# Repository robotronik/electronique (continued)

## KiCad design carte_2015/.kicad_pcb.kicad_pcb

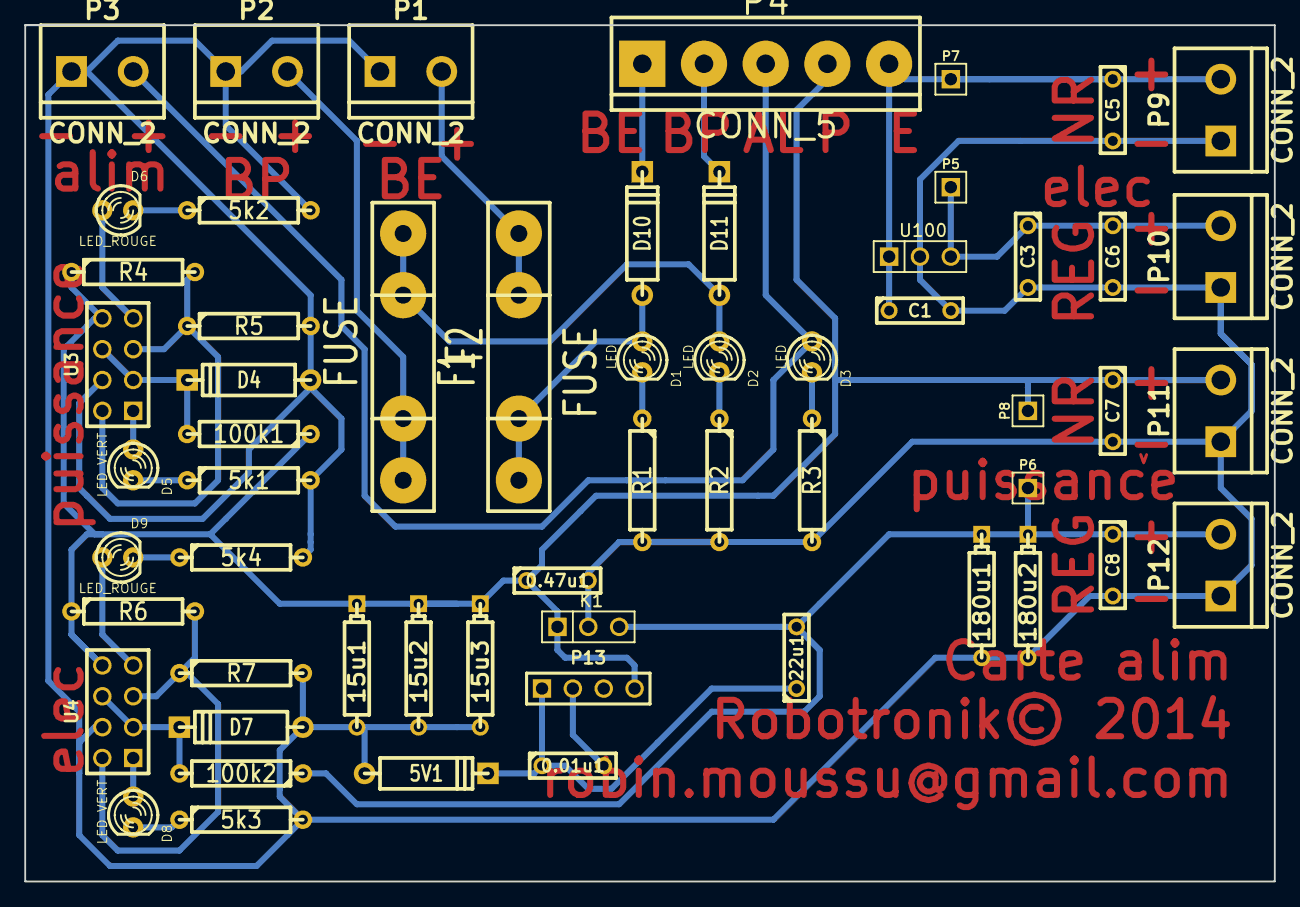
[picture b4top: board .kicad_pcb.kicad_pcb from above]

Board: 2 copper layers, 102.9 x 70.5 mm, 58 parts (0 on the bottom side), 29 nets.

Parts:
0.01u1, 0.47u1: C; C2
5V1: ZENER; D4
5k1, 5k2, 5k3, 5k4, 100k1, 100k2: R; R4
15u1, 15u2, 15u3, 180u1, 180u2: CP1; CP4
22u1: INDUCTOR; C2
C1, C3, C5, C6, C7, C8: C; C2
D1, D2, D3: LED; LED-3MM
D4, D7: ZENER; D4
D5, D8: LED_VERT; LED-3MM
D6, D9: LED_ROUGE; LED-3MM
D10, D11: DIODE; D4
F1, F2: FUSE; FUSE5-20
K1: CONN_3; PIN_ARRAY_3X1
P1, P2, P3, P9, P10, P11, P12: CONN_2; bornier2
P4: CONN_5; bornier5
P5, P6, P7, P8: CONN_1; PIN_ARRAY_1
P13: CONN_4; PIN_ARRAY_4x1
R1, R2, R3, R4, R5, R6, R7: R; R4
U3, U4: TL072; pin_array_4x2
U100: 7905_CORRIGE; PIN_ARRAY_3X1

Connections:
/alim_elec: C3.1, C6.1, P5.1, P10.2, U100.3
/alim_elec_non_regul: C1.1, C5.1, P4.5, P7.1, P9.2, U100.1
/alim_puissance_non_regul: 0.47u1.1, 15u1.1, 15u2.1, 15u3.1, 100k1.1, C7.1, K1.1, P4.4, P8.1, P11.2, P13.4, R4.1, R6.1, U3.8, U4.8
/alim_puissance_regul: 22u1.2, 100k2.1, 180u1.1, 180u2.1, C8.1, K1.3, P6.1, P12.2
GND: 0.47u1.2, 5V1.1, 5k1.2, 5k2.2, 5k3.2, 5k4.2, 15u1.2, 15u2.2, 15u3.2, 180u1.2, 180u2.2, C1.2, C3.2, C5.2, C6.2, C7.2, C8.2, D4.1, D7.1, K1.2, P1.1, P2.1, P3.1, P9.1, P10.1, P11.1, P12.1, R1.2, R2.2, R3.2, R5.2, R7.2, U3.4, U4.4, U100.2
unnamed: 100k2.2, D7.2, U4.3, U4.6
unnamed: 5k3.1, D8.2
unnamed: 5k4.1, D9.2
unnamed: D9.1, U4.7
unnamed: D8.1, U4.1
unnamed: R6.2, R7.1, U4.2, U4.5
unnamed: 5k1.1, D5.2
unnamed: 5k2.1, D6.2
unnamed: D6.1, U3.7
unnamed: D5.1, U3.1
unnamed: 100k1.2, D4.2, U3.3, U3.6
unnamed: R4.2, R5.1, U3.2, U3.5
unnamed: D11.2, P4.2
unnamed: D10.2, P4.1
unnamed: 0.01u1.2, P13.2
unnamed: 0.01u1.1, 5V1.2, 22u1.1, P13.1
unnamed: D2.1, D11.1, F2.2
unnamed: D1.1, D10.1, F1.2
unnamed: D1.2, R1.1
unnamed: D2.2, R2.1
unnamed: D3.2, R3.1
unnamed: F1.1, P1.2
unnamed: F2.1, P2.2
unnamed: D3.1, P3.2, P4.3
